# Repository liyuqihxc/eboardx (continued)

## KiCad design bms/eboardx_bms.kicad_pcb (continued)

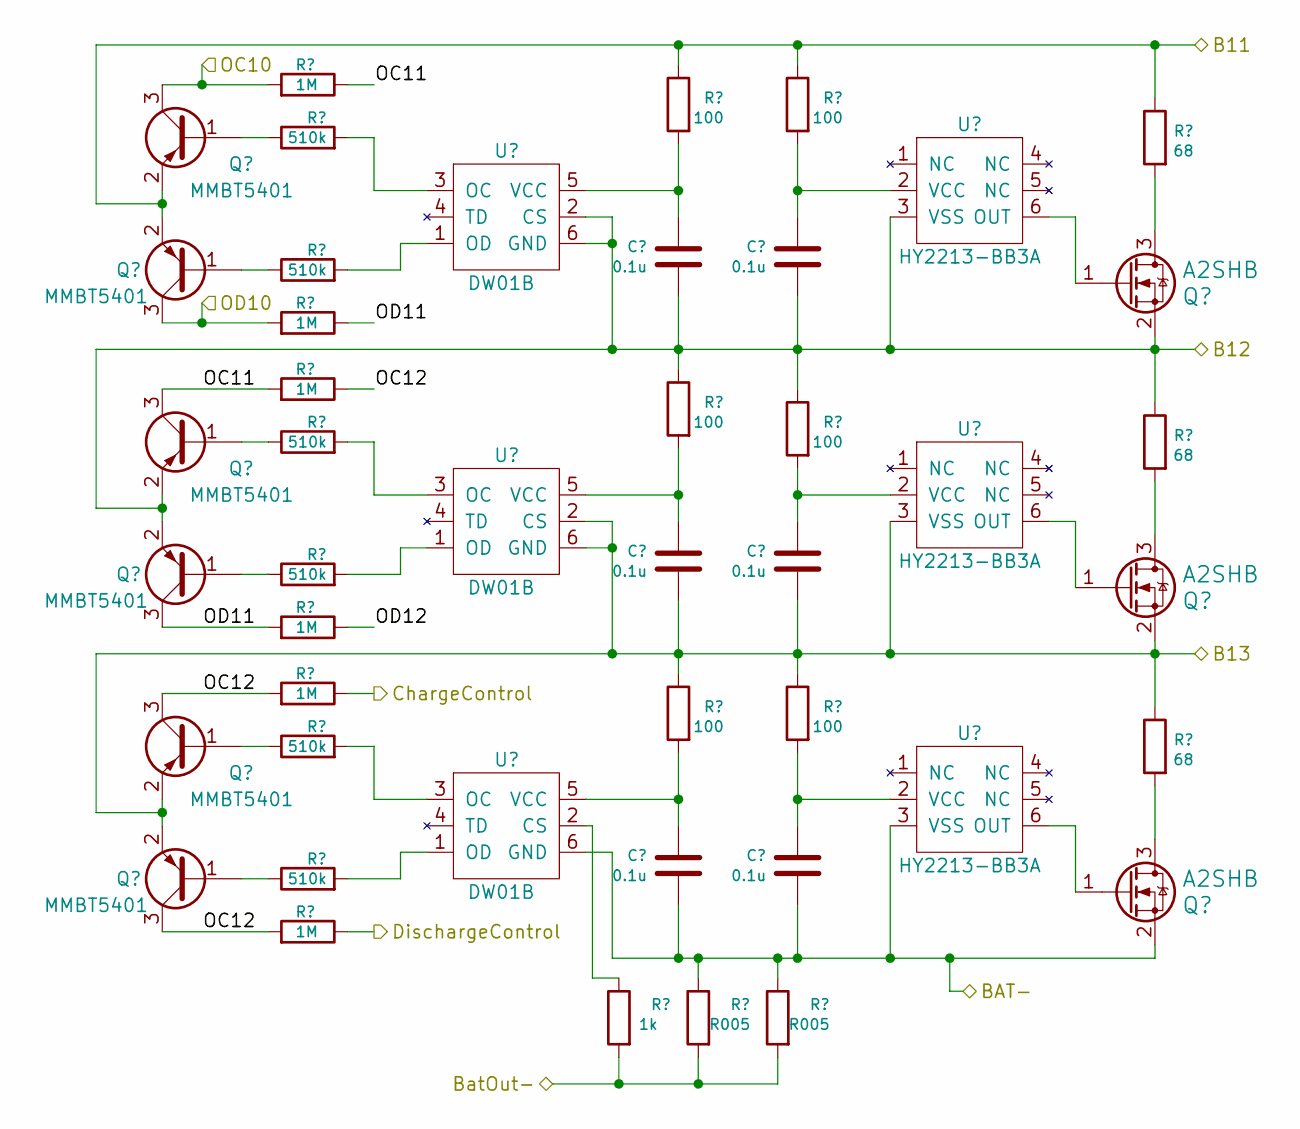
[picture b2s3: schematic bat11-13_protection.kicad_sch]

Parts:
C11, C12, C13, C24, C25, C26: 0.1u; C_0603_1608Metric
Q21, Q22, Q23: A2SHB; SOT-23
Q44, Q45, Q46, Q47, Q48, Q49: MMBT5401; SOT-23
R11, R12, R13, R24, R25, R26: 100; R_0603_1608Metric
R37, R38, R39: 68; R_2512_6332Metric
R60, R61, R62, R63, R64, R65: 510k; R_0603_1608Metric
R86, R87, R88, R89, R90, R91: 1M; R_0603_1608Metric
R101: 1k; R_0603_1608Metric
R102, R103: R005; R_2512_6332Metric
U11, U12, U13: DW01B; SOT-23-6
U24, U25, U26: HY2213-BB3A; SOT-23-6

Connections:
/BAT11: Q44.2 (E), Q45.2 (E), R11.1, R24.1, R37.1; also elsewhere on the board
/BAT12: C11.2, C24.2, Q21.2 (S), Q46.2 (E), Q47.2 (E), R12.1, R25.1, R38.1, U11.2 (CS), U11.6 (GND), U24.3 (VSS); also elsewhere on the board
/BAT13: C12.2, C25.2, Q22.2 (S), Q48.2 (E), Q49.2 (E), R13.1, R26.1, R39.1, U12.2 (CS), U12.6 (GND), U25.3 (VSS); also elsewhere on the board
/BAT-: C13.2, C26.2, Q23.2 (S), R102.1, R103.1, U13.6 (GND), U26.3 (VSS); also elsewhere on the board
/BatOut-: R101.2, R102.2, R103.2; also elsewhere on the board
/ChargeControl: R90.1; also elsewhere on the board
/DischargeControl: R91.1; also elsewhere on the board
/Protection for BAT1-10/OC10: Q45.3 (C), R87.2; also elsewhere on the board
/Protection for BAT1-10/OD10: Q44.3 (C), R86.2; also elsewhere on the board
/Protection for BAT11-13/OC11: Q46.3 (C), R86.1, R88.2
/Protection for BAT11-13/OC12: Q48.3 (C), Q49.3 (C), R88.1, R90.2, R91.2
/Protection for BAT11-13/OD11: Q47.3 (C), R87.1, R89.2
/Protection for BAT11-13/OD12: R89.1
unnamed: Q21.3 (D), R37.2
unnamed: Q21.1 (G), U24.6 (OUT)
unnamed: Q22.3 (D), R38.2
unnamed: Q22.1 (G), U25.6 (OUT)
unnamed: Q23.3 (D), R39.2
unnamed: Q23.1 (G), U26.6 (OUT)
unnamed: Q44.1 (B), R60.1
unnamed: Q45.1 (B), R61.1
unnamed: Q46.1 (B), R62.1
unnamed: Q47.1 (B), R63.1
unnamed: Q48.1 (B), R64.1
unnamed: Q49.1 (B), R65.1
unnamed: R60.2, U11.3 (OC)
unnamed: R61.2, U11.1 (OD)
unnamed: C11.1, R11.2, U11.5 (VCC)
unnamed: R62.2, U12.3 (OC)
unnamed: R63.2, U12.1 (OD)
unnamed: C12.1, R12.2, U12.5 (VCC)
unnamed: R101.1, U13.2 (CS)
unnamed: R64.2, U13.3 (OC)
unnamed: R65.2, U13.1 (OD)
unnamed: C13.1, R13.2, U13.5 (VCC)
unnamed: C24.1, R24.2, U24.2 (VCC)
unnamed: C25.1, R25.2, U25.2 (VCC)
unnamed: C26.1, R26.2, U26.2 (VCC)

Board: 2 copper layers, 214 parts (0 on the bottom side), 156 nets, no tracks yet.

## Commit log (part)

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2020-02-25 init
2020-02-25 [bms]init
2020-02-25 [bms]cmake config change
2020-04-10 spot welder
2021-04-16 code
2023-06-20 migrate to kicad7
2023-09-14 bms schematic
2023-09-16 update pcb footprints
2023-09-17 bms change to 13s1p
2023-09-25 bms pcb
